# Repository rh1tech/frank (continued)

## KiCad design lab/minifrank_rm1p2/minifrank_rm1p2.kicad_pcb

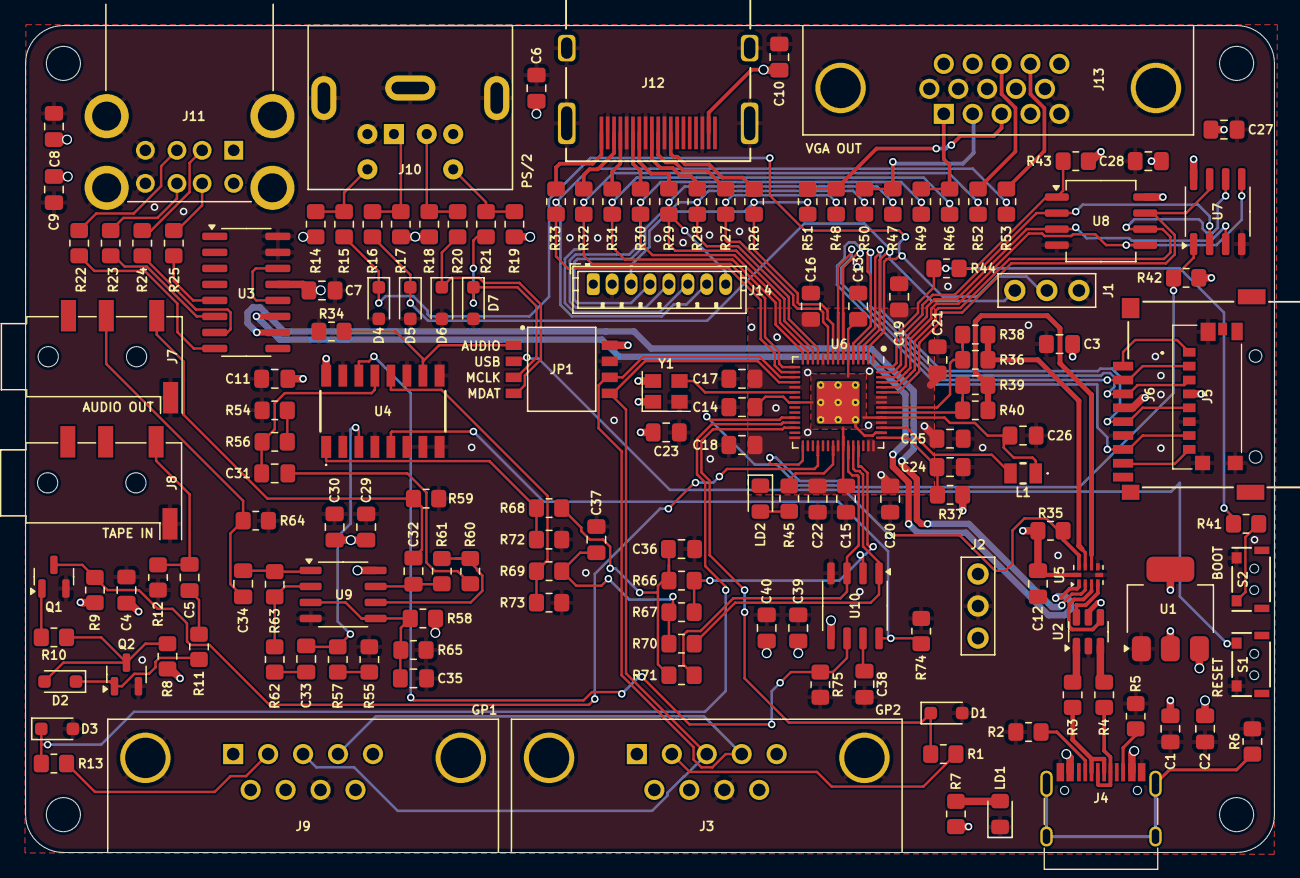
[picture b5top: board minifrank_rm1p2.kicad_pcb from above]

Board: 4 copper layers, 99.0 x 65.5 mm, 159 parts (0 on the bottom side), 116 nets.

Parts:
C1, C2, C8, C9, C29, C31, C32, C33, C34, C35, C38, C39: 10u; Capacitor (0805)
C3, C4, C5, C6, C10, C11, C12, C13, C15, C16, C17, C18, C19, C20, C21, C22, C23, C27, C28, C30, C40: 100n; Capacitor (0805)
C7, C14, C24, C25, C26: 4.7u; Capacitor (0805)
C36, C37: 47n; Capacitor (0805)
D1, D3, D4, D5, D6, D7: 3V3; Diode (SOD-323)
D2: 1N4148; Diode (SOD-323)
H1, H2, H3, H4: MountingHole; Mounting Hole (2.7mm)
J1: UART; Pin Header (1x03)
J2: PWR; Pin Header (1x03)
J3, J9: D-SUB 9 Male; D-SUB (9 pin, male, top mount)
J4: USB4215-03-A; USB Type C
J5: 0475710001; MicroSD (SMD, short)
J6: 104031-0811; MicroSD (SMD, long)
J7, J8: PJ-320D; Jack (3.5mm, PJ-320D)
J10: MDC-036; MiniDIN (6 Pin, female)
J11: SS-52100-004; USB Type A (stacked)
J12: DC3RX19JA2; HDMI (female)
J13: D-SUB 15 Female; D-SUB (15 pin, female)
J14: Pin Header 1x08; Connector Female ZH 1.50mm (8 pins)
JP1: Main Jumpers; SW_DS05-127-2-04BK-SMT-TR
L1: 3.3u; Inductor (0806)
LD1: Power; LED (0805)
LD2: Blue; LED (0805)
Q1, Q2: BC850; SOT-23
R1, R7, R9, R13, R14, R17, R18, R19, R41, R45, R49, R50, R51, R70, R71: 1K; Resistor (0805)
R2, R5: 5.1K; Resistor (0805)
R3, R4, R22, R23, R24, R25: 22R; Resistor (0805)
R6: 1M; Resistor (0805)
R8, R10, R11, R34, R35, R42, R43, R56, R57, R58, R60, R62, R65, R68, R69: 10K; Resistor (0805)
R12, R15, R16, R20, R21, R52, R53: 100R; Resistor (0805)
R26, R27, R28, R29, R30, R31, R32, R33: 270R; Resistor (0805)
R36, R39: 150R; Resistor (0805)
R37: 33; Resistor (0805)
R38, R40: 33R; Resistor (0805)
R44: 0R; Resistor (0805)
R46, R47, R48: 330R; Resistor (0805)
R54, R55, R66, R67, R72, R73: 2K; Resistor (0805)
R59, R64: 20K; Resistor (0805)
R61, R63: 47K; Resistor (0805)
R74, R75: 470R; Resistor (0805)
S1: Reset; TACT-SIDE-4623
S2: TS-1233; TACT-SIDE-4623
U1: NCP1117 3.3; SOT-223
U2: USBLC6-2SC6; SOT-23-6
U3: MW7211A; SOP-16
U4: 74HC4052D; 74HC4052D653
U5: TS3USB221RSER; UQFN-10
U6: RP2350; QFN 60 (RP2350A)
U7: ESP-PSRAM32; SO-8
U8: W25Q128JVS; SOIC-8
U9: LM358; SO-8
U10: TDA1387T; SO-8
Y1: ASE-12MHz; Crystal (3225, active)

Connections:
+1V1: C13.1, C14.1, C15.1, C26.1, L1.1, U6.6 (DVDD), U6.23 (DVDD), U6.39 (DVDD), U6.50 (VREG_FB)
+3V3: C1.1, C3.2, C4.1, C11.2, C12.2, C16.1, C17.1, C18.1, C19.1, C20.1, C21.1, C22.1, C23.1, C25.1, C27.1, C28.1, J2.1, J5.P4 (VDD), J6.4 (VDD), JP1.8, R7.2, R8.1, R9.1, R35.1, R37.1, R42.2, R43.1, U1.2 (VO), U4.16 (VCC), U5.10 (VCC), U6.1 (IOVDD), U6.11 (IOVDD), U6.20 (IOVDD), U6.30 (IOVDD), U6.38 (IOVDD), U6.44 (ADC_AVDD), U6.45 (IOVDD), U6.49 (VREG_VIN), U6.53 (USB_OTP_VDD), U6.54 (QSPI_IOVDD), U7.8 (VCC), U8.8 (VCC), Y1.1 (EN), Y1.4 (Vdd)
/AMP_IN_L: C31.1, R56.1, U4.13 (1Z)
/AMP_IN_R: C33.1, R57.1, U4.3 (2Z)
/AUDIOSW: JP1.1, R34.2, U4.10 (S0)
/Audio Out/AMP_OUTL: C32.2, J7.T, R59.2
/Audio Out/AMP_OUTR: C34.2, J7.R, R64.2
/D+: R36.1, R38.1, U5.8 (D+)
/D-: R39.1, R40.1, U5.7 (D-)
/GPIO0: D4.1 (K), J1.2, R15.2, U6.2 (GPIO0)
/GPIO1: D5.1 (K), J1.3, R16.2, U6.3 (GPIO1)
/GPIO2: J5.P5 (CLK), J6.5 (CLK), U6.4 (GPIO2)
/GPIO3: J5.P3 (CMD), J6.3 (CMD), U6.5 (GPIO3)
/GPIO4: J5.P7 (DAT0), J6.7 (DAT0), U6.7 (GPIO4)
/GPIO5: J5.P2 (CD/DAT3), J6.2 (DAT3/CD), U6.8 (GPIO5)
/GPIO6: J14.3, R26.2, R51.1, U6.9 (GPIO6)
/GPIO7: R27.2, R48.1, U6.10 (GPIO7)
/GPIO8: J14.4, R28.2, R50.1, U6.12 (GPIO8)
/GPIO9: J14.8, R29.2, R47.1, U6.13 (GPIO9)
/GPIO10: J14.5, R30.2, R49.1, U6.14 (GPIO10)
/GPIO11: R31.2, R46.1, U6.15 (GPIO11)
/GPIO12: J14.6, R32.2, R52.2, U6.16 (GPIO12)
/GPIO13: J14.7, R33.2, R53.2, U6.17 (GPIO13)
/GPIO14: J3.4, J9.4, JP1.6, U6.18 (GPIO14)
/GPIO15: J3.3, J9.3, JP1.5, U6.19 (GPIO15)
/GPIO16: D3.1 (K), R13.1, U6.27 (GPIO16)
/GPIO17: D1.1 (K), R1.1, U6.28 (GPIO17)
/GPIO19: R42.1, U6.31 (GPIO19), U7.1 (~CE)
/GPIO22: Q1.3 (C), R9.2, U6.34 (GPIO22)
/GPIO26: R71.2, U6.40 (GPIO26_ADC0), U10.3 (DATA)
/GPIO27: R70.2, U6.41 (GPIO27_ADC1), U10.1 (SCLK)
/GPIO28: R66.1, R67.1, U6.42 (GPIO28_ADC2), U10.2 (LRCK)
/HUB_D+: U3.11 (DPU), U5.1 (1D+)
/HUB_D-: U3.10 (DMU), U5.2 (1D-)
/KB_CLK: J10.5, R14.2, R15.1
/KB_DATA: J10.1, R16.1, R17.2
/MS_CLK: J10.6, R19.2, R21.1
/MS_CLK_3V: D7.1 (K), JP1.3, R21.2
/MS_DATA: J10.2, R18.2, R20.1
/MS_DATA_3V: D6.1 (K), JP1.4, R20.2
/PWM_OUT_L: R69.2, R73.1, U4.12 (1Y0)
/PWM_OUT_R: R68.2, R72.1, U4.1 (2Y0)
/RP2350A/FLASH_SS: R43.2, R44.2, U8.1 (~CS)
/RP2350A/QSPI_SCLK: U6.56 (QSPI_SCLK), U7.6 (SCLK), U8.6 (CLK)
/RP2350A/QSPI_SD0: U6.57 (QSPI_SD0), U7.5 (SI/SIO), U8.5 (DI(IO0))
/RP2350A/QSPI_SD1: U6.59 (QSPI_SD1), U7.2 (SO/SIO), U8.2 (DO(IO1))
/RP2350A/QSPI_SD2: U6.58 (QSPI_SD2), U7.3 (SIO2), U8.3 (IO2)
/RP2350A/QSPI_SD3: U6.55 (QSPI_SD3), U7.7 (SIO3), U8.7 (IO3)
/RP2350A/QSPI_SS: R41.1, R44.1, U6.60 (QSPI_SS)
/RP2350A/VREG_AVDD: C24.1, R37.2, U6.46 (VREG_AVDD)
/RP2350A/VREG_LX: L1.2, U6.48 (VREG_LX)
/RP2350A/XIN: U6.21 (XIN), Y1.3 (OUT)
/RP2350A/~USB_BOOT: R41.2, S2.2
/RUN: S1.1, U6.26 (RUN)
/SD Card/DAT1: J5.P8 (DAT1), J6.8 (DAT1)
/SD Card/DAT2: J5.P1 (DAT2), J6.1 (DAT2)
/TDA_L: R75.2, U4.14 (1Y1), U10.6 (A_LEFT)
/TDA_R: R74.1, U4.5 (2Y1), U10.8 (A_RIGHT)
/USBMPXSW: JP1.2, R35.2, U5.9 (S)
/USB_D1+: R22.1, U3.8 (DP3)
/USB_D1-: R24.1, U3.7 (DM3)
/USB_D2+: R23.1, U3.6 (DP2)
/USB_D2-: R25.1, U3.5 (DM2)
/UTC_D+: U2.4 (I/O2), U5.3 (2D+)
/UTC_D-: U2.6 (I/O1), U5.4 (2D-)
GND: C1.2, C2.2, C3.1, C4.2, C6.2, C7.2, C8.2, C9.2, C10.2, C11.1, C12.1, C13.2, C14.2, C15.2, C16.2, C17.2, C18.2, C19.2, C20.2, C21.2, C22.2, C23.2, C24.2, C25.2, C26.2, C27.2, C28.2, C29.1, C30.1, C35.1, C36.2, C37.2, C38.2, C39.2, C40.2, D1.2 (A), D3.2 (A), D4.2 (A), D5.2 (A), D6.2 (A), D7.2 (A), J1.1, J2.2, J3.8, J4.1 (GND), J4.12 (GND), J5.G1 (GND_1), J5.G2 (GND_2), J5.G3 (GND_3), J5.P6 (VSS), J6.6 (VSS), J7.S, J8.S, J9.8, J10.3, J11.4 (GND1), J11.8 (GND2), J11.9 (Shield), J12.2 (G_D2), J12.5 (G_D1), J12.8 (G_D0), J12.11 (G_CLK), J12.17 (G_DDC/CEC), J12.20 (SHIELD1), J12.21 (SHIELD2), J12.22 (SHIELD3), J12.23 (SHIELD4), J13.0, J13.5, J13.6, J13.7, J13.8, J13.10, J14.2, JP1.7, LD1.1 (K), LD2.1 (K), Q1.2 (E), Q2.2 (E), R2.1, R5.1, R6.2, R12.2, R34.1, R54.2, R55.2, R59.1, R64.1, R65.1, R72.2, R73.2, R74.2, R75.1, S1.2, S2.1, U1.1 (GND), U2.2 (GND), U3.15 (GND), U3.16 (GND), U4.2 (2Y2), U4.4 (2Y3), U4.6 (~E), U4.7 (VEE), U4.8 (GND), U4.9 (S1), U4.11 (1Y3), U4.15 (1Y2), U5.5 (GND), U5.6 (~OE), U6.47 (VREG_PGND), U6.61 (GND), U7.4 (VSS), U8.4 (GND), U9.4 (V-), U10.4 (AGND), Y1.2 (GND)
GPIO25: R45.2, U6.37 (GPIO25)
unnamed: C5.1, J8.T, R12.1
unnamed: C5.2, R11.1
unnamed: C31.2, R60.2
unnamed: C32.1, R61.1, U9.7
unnamed: C33.2, R62.2
unnamed: C34.1, R63.1, U9.1
unnamed: C36.1, R66.2, R68.1, R71.1
unnamed: C37.1, R67.2, R69.1, R70.1
unnamed: D2.2 (A), Q2.3 (C), R8.2, R10.1
unnamed: D2.1 (K), Q2.1 (B), R11.2
unnamed: J3.2, R1.2
unnamed: J4.4 (CC1), R2.2
unnamed: J4.10 (CC2), R5.2
unnamed: J4.5 (DN2), J4.7 (DN1), R3.2
unnamed: J4.6 (DP1), J4.8 (DP2), R4.2
unnamed: J4.13 (SHIELD), R6.1
unnamed: J9.2, R13.2
unnamed: J11.3 (D1+), R22.2
unnamed: J11.2 (D1-), R24.2
unnamed: J11.7 (D2+), R23.2
unnamed: J11.6 (D2-), R25.2
unnamed: J12.12 (CLKN), R26.1
unnamed: J12.10 (CLKP), R27.1
unnamed: J12.9 (D0N), R28.1
unnamed: J12.7 (D0P), R29.1
unnamed: J12.6 (D1N), R30.1
unnamed: J12.4 (D1P), R31.1
unnamed: J12.3 (D2N), R32.1
unnamed: J12.1 (D2P), R33.1
unnamed: J13.1, R46.2, R49.2
unnamed: J13.2, R47.2, R50.2
unnamed: J13.3, R48.2, R51.2
unnamed: J13.13, R52.1
unnamed: J13.14, R53.1
unnamed: LD1.2 (A), R7.1
unnamed: LD2.2 (A), R45.1
unnamed: Q1.1 (B), R10.2
unnamed: R3.1, U2.1 (I/O1)
unnamed: R4.1, U2.3 (I/O2)
unnamed: R54.1, R56.2
unnamed: R55.1, R57.2
unnamed: U3.12 (VD33), U3.14 (VD3)
unnamed: R39.2, R40.2, U6.51 (USB_DM)
unnamed: R36.2, R38.2, U6.52 (USB_DP)
unnamed: C35.2, R58.1, R65.2, U9.3 (+), U9.5 (+)
unnamed: R62.1, R63.2, U9.2 (-)
unnamed: R60.1, R61.2, U9.6 (-)
unnamed: C38.1, U10.7 (FLT)
VBUS: C2.1, C6.1, C7.1, C8.1, C9.1, C10.1, C29.2, C30.2, C39.1, C40.1, J2.3, J3.6, J4.2 (VBUS), J4.11 (VBUS), J9.6, J10.4, J11.1 (VBUS1), J11.5 (VBUS2), J12.18 (+5V), J14.1, R14.1, R17.1, R18.1, R19.1, R58.2, U1.3 (VI), U2.5 (VBUS), U3.13 (VDD5), U9.8 (V+), U10.5 (VA)

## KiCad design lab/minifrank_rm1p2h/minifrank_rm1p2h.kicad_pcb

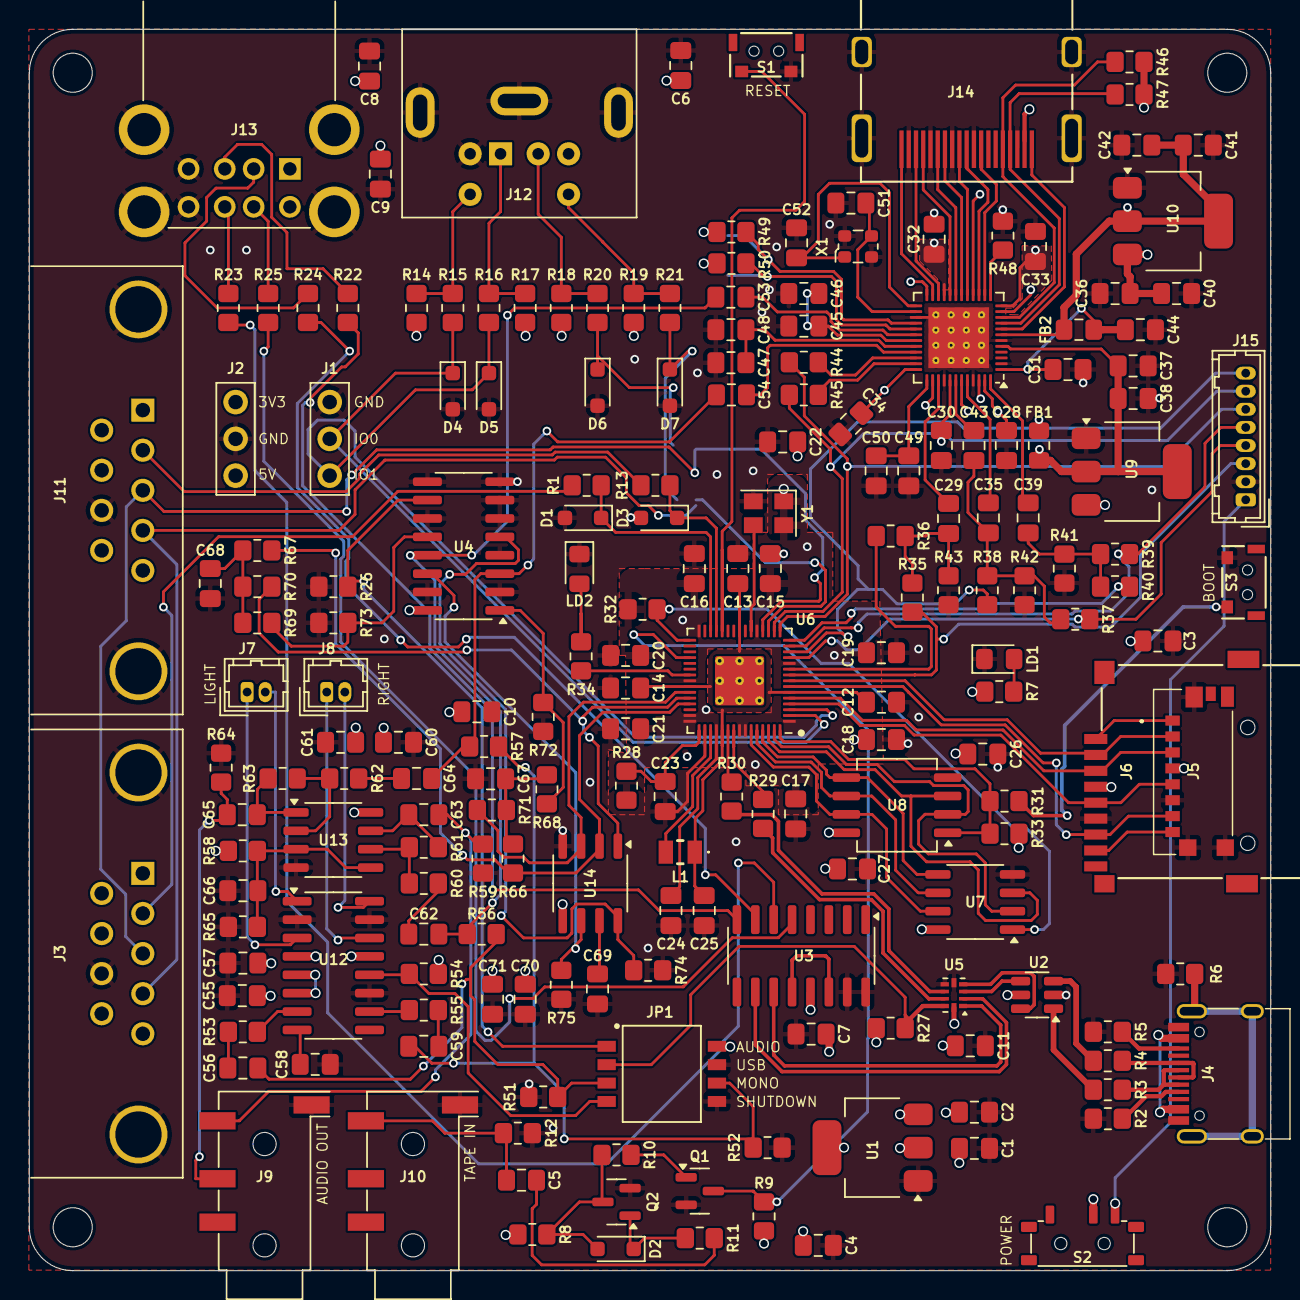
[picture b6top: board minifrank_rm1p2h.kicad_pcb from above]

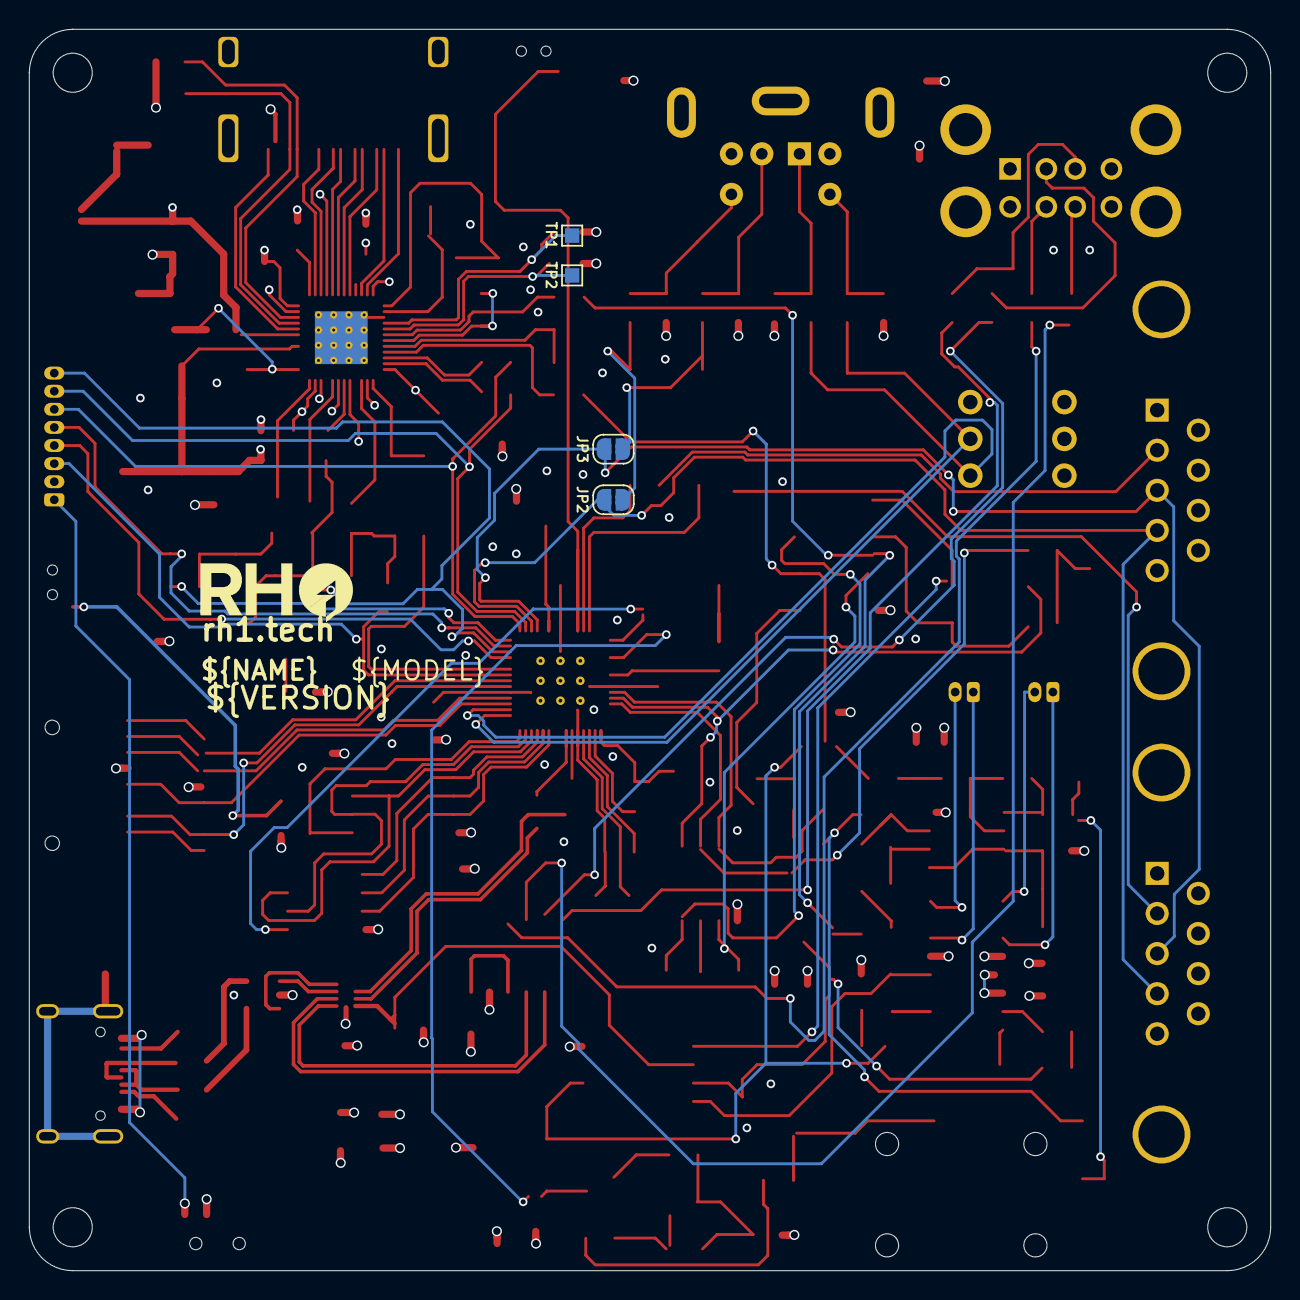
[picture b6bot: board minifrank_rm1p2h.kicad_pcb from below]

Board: 4 copper layers, 85.8 x 85.8 mm, 203 parts (4 on the bottom side), 148 nets.

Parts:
C1, C2, C8, C9, C28, C36, C37, C41, C44, C60, C62, C63, C64, C65, C66, C69, C70: 10u; Capacitor (0805)
C3, C4, C5, C6, C10, C11, C12, C14, C15, C16, C17, C18, C19, C20, C21, C22, C26, C27, C29, C30, C31, C32, C33, C34, C35, C39, C40, C58, C61, C71: 100n; Capacitor (0805)
C7, C13, C23, C24, C25, C46, C48, C50: 4.7u; Capacitor (0805)
C38, C42, C53, C54, C55, C56, C59: 1u; Capacitor (0805)
C43: 1n; Capacitor (0805)
C45, C47, C49: 220n; Capacitor (0805)
C51, C52: 15p; Capacitor (0805)
C57: 47u; Capacitor (0805)
C67, C68: 47n; Capacitor (0805)
D1, D3, D4, D5, D6, D7: 3V3; Diode (SOD-323)
D2: 1N4148; Diode (SOD-323)
FB1, FB2: 220R; Inductor (0805)
H1, H2, H3, H4: MountingHole; Mounting Hole (2.7mm)
J1: UART; Pin Header (1x03)
J2: PWR; Pin Header (1x03)
J3, J11: D-SUB 9 Male; D-SUB (9 pin, male, top mount)
J4: USB4215-03-A; USB Type C
J5: 0475710001; MicroSD (SMD, short)
J6: 104031-0811; MicroSD (SMD, long)
J7: PAM L; Connector Female 1.25 JST 2P
J8: PAM R; Connector Female 1.25 JST 2P
J9, J10: PJ-320D; Jack (3.5mm, PJ-320D)
J12: MDC-036; MiniDIN (6 Pin, female)
J13: SS-52100-004; USB Type A (stacked)
J14: DC3RX19JA2; HDMI (female)
J15: Pin Header 1x08; Connector Female 1.25 JST 8P
JP1: Main Jumpers; SW_DS05-127-2-04BK-SMT-TR
JP2: Mouse CLK; Jumper (solder)
JP3: Mouse DATA; Jumper (solder)
L1: 3.3u; Inductor (0806)
LD1: Power; LED (0805)
LD2: Blue; LED (0805)
Q1, Q2: BC850; SOT-23
R1, R7, R9, R13, R14, R17, R18, R19, R31, R34, R48, R70, R71: 1K; Resistor (0805)
R2, R5: 5.1K; Resistor (0805)
R3, R4, R22, R23, R24, R25: 22R; Resistor (0805)
R6: 1M; Resistor (0805)
R8, R10, R11, R26, R27, R32, R33, R53, R54, R55, R56, R57, R58, R60, R62, R65, R68, R69: 10K; Resistor (0805)
R12, R15, R16, R20, R21, R44, R45: 100R; Resistor (0805)
R28: 33; Resistor (0805)
R29, R30: 27R; Resistor (0805)
R35, R37, R39: 800R; Resistor (0805)
R36, R38, R40: 400R; Resistor (0805)
R41, R42, R43: 75R; Resistor (0805)
R46, R47, R51, R52, R66, R67, R72, R73: 2K; Resistor (0805)
R49, R50: 4.7K; Resistor (0805)
R59, R64: 20K; Resistor (0805)
R61, R63: 47K; Resistor (0805)
R74, R75: 470R; Resistor (0805)
S1: Reset; TACT-SIDE-4623
S2: MSK12C02; Switch (MSK12C02)
S3: TS-1233; TACT-SIDE-4623
TP1: MS9288_SCL; TestPoint (Pad 1.0x1.0mm)
TP2: MS9288_SDA; TestPoint (Pad 1.0x1.0mm)
U1: NCP1117 3.3; SOT-223
U2: USBLC6-2SC6; SOT-23-6
U3: MW7211A; SOP-16
U4: 74HC4052D; SOP-16
U5: TS3USB221RSER; UQFN-10
U6: RP2350; QFN 60 (RP2350A)
U7: ESP-PSRAM32; SO-8
U8: W25Q128JVS; SOIC-8
U9: AMS1117-3.3; SOT-223
U10: AMS1117-1.8; SOT-223
U11: MS9288A; QFN 48
U12: PAM8403D; SOP-16
U13: LM358; SO-8
U14: TDA1387T; SO-8
X1: 24.576 MHz; Crystal (2520)
Y1: ASE-12MHz; Crystal (3225, active)

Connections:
+1V1: C12.1, C13.1, C14.1, C25.1, L1.1, U6.6 (DVDD), U6.23 (DVDD), U6.39 (DVDD), U6.50 (VREG_FB)
+3V3: C1.1, C3.2, C4.1, C10.2, C11.2, C15.1, C16.1, C17.1, C18.1, C19.1, C20.1, C21.1, C22.1, C24.1, C26.1, C27.1, J2.1, J5.P4 (VDD), J6.4 (VDD), JP1.8, R7.2, R8.1, R9.1, R27.1, R28.1, R32.2, R33.1, U1.2 (VO), U4.16 (VCC), U5.10 (VCC), U6.1 (IOVDD), U6.11 (IOVDD), U6.20 (IOVDD), U6.30 (IOVDD), U6.38 (IOVDD), U6.44 (ADC_AVDD), U6.45 (IOVDD), U6.49 (VREG_VIN), U6.53 (USB_OTP_VDD), U6.54 (QSPI_IOVDD), U7.8 (VCC), U8.8 (VCC), Y1.1 (EN), Y1.4 (Vdd)
/AMP_IN_L: C53.2, C62.1, R56.1, U4.13 (1Z)
/AMP_IN_R: C54.2, C64.1, R57.1, U4.3 (2Z)
/AUDIOSW: JP1.1, R26.2, U4.10 (S0)
/Audio Out/AMP_OUTL: C63.2, J9.T, R59.2
/Audio Out/AMP_OUTR: C65.2, J9.R, R64.2
/Audio Out/AMP_PAM_OUTL_M: J7.2, U12.3 (-OUTL)
/Audio Out/AMP_PAM_OUTL_P: J7.1, U12.1 (+OUT_L)
/Audio Out/AMP_PAM_OUTR_M: J8.2, U12.14 (-OUT_R)
/Audio Out/AMP_PAM_OUTR_P: J8.1, U12.16 (+OUT_R)
/D+: R29.1, U5.8 (D+)
/D-: R30.1, U5.7 (D-)
/DAT1: J5.P8 (DAT1), J6.8 (DAT1)
/DAT2: J5.P1 (DAT2), J6.1 (DAT2)
/GPIO0: D4.1 (K), J1.2, R15.2, U6.2 (GPIO0)
/GPIO1: D5.1 (K), J1.3, R16.2, U6.3 (GPIO1)
/GPIO2: J5.P5 (CLK), J6.5 (CLK), U6.4 (GPIO2)
/GPIO3: J5.P3 (CMD), J6.3 (CMD), U6.5 (GPIO3)
/GPIO4: J5.P7 (DAT0), J6.7 (DAT0), U6.7 (GPIO4)
/GPIO5: J5.P2 (CD/DAT3), J6.2 (DAT3/CD), U6.8 (GPIO5)
/GPIO6: J15.3, R35.1, U6.9 (GPIO6)
/GPIO7: R36.1, U6.10 (GPIO7)
/GPIO8: J15.4, R37.1, U6.12 (GPIO8)
/GPIO9: J15.8, R38.1, U6.13 (GPIO9)
/GPIO10: J15.5, R39.1, U6.14 (GPIO10)
/GPIO11: R40.1, U6.15 (GPIO11)
/GPIO12: J15.6, R44.1, U6.16 (GPIO12)
/GPIO13: J15.7, R45.1, U6.17 (GPIO13)
/GPIO14: J3.4, J11.4, JP2.2 (B), U6.18 (GPIO14)
/GPIO15: J3.3, J11.3, JP3.2 (B), U6.19 (GPIO15)
/GPIO16: D3.1 (K), R13.1, U6.27 (GPIO16)
/GPIO17: D1.1 (K), R1.1, U6.28 (GPIO17)
/GPIO19: R32.1, U6.31 (GPIO19), U7.1 (~CE)
/GPIO22: Q1.3 (C), R9.2, U6.34 (GPIO22)
/GPIO26: R71.2, U6.40 (GPIO26_ADC0), U14.3 (DATA)
/GPIO27: R70.2, U6.41 (GPIO27_ADC1), U14.1 (SCLK)
/GPIO28: R66.1, R67.1, U6.42 (GPIO28_ADC2), U14.2 (LRCK)
/HUB_D+: U3.11 (DPU), U5.1 (1D+)
/HUB_D-: U3.10 (DMU), U5.2 (1D-)
/KB_CLK: J12.5, R14.2, R15.1
/KB_DATA: J12.1, R16.1, R17.2
/MONO_L: C56.1, JP1.3, R51.1, R56.2
/MONO_R: C59.1, JP1.6, R52.1, R57.2
/MS_CLK: J12.6, R19.2, R21.1
/MS_CLK_3V: D7.1 (K), JP2.1 (A), R21.2
/MS_DATA: J12.2, R18.2, R20.1
/MS_DATA_3V: D6.1 (K), JP3.1 (A), R20.2
/PWM_OUT_L: R69.2, R73.1, U4.12 (1Y0)
/PWM_OUT_R: R68.2, R72.1, U4.1 (2Y0)
/RP2350A/QSPI_SCLK: U6.56 (QSPI_SCLK), U7.6 (SCLK), U8.6 (CLK)
/RP2350A/QSPI_SD0: U6.57 (QSPI_SD0), U7.5 (SI/SIO), U8.5 (DI(IO0))
/RP2350A/QSPI_SD1: U6.59 (QSPI_SD1), U7.2 (SO/SIO), U8.2 (DO(IO1))
/RP2350A/QSPI_SD2: U6.58 (QSPI_SD2), U7.3 (SIO2), U8.3 (IO2)
/RP2350A/QSPI_SD3: U6.55 (QSPI_SD3), U7.7 (SIO3), U8.7 (IO3)
/RP2350A/QSPI_SS: R31.1, R33.2, U6.60 (QSPI_SS), U8.1 (~CS)
/RP2350A/VREG_AVDD: C23.1, R28.2, U6.46 (VREG_AVDD)
/RP2350A/VREG_LX: L1.2, U6.48 (VREG_LX)
/RP2350A/XIN: U6.21 (XIN), Y1.3 (OUT)
/RP2350A/~USB_BOOT: R31.2, S3.2
/RUN: S1.1, U6.26 (RUN)
/SHND: JP1.4, R54.2, U12.12 (SHND)
/TDA_L: R75.2, U4.14 (1Y1), U14.6 (A_LEFT)
/TDA_R: R74.1, U4.5 (2Y1), U14.8 (A_RIGHT)
/USBMPXSW: JP1.2, R27.2, U5.9 (S)
/USB_D1+: R22.1, U3.8 (DP3)
/USB_D1-: R24.1, U3.7 (DM3)
/USB_D2+: R23.1, U3.6 (DP2)
/USB_D2-: R25.1, U3.5 (DM2)
/UTC_D+: U2.4 (I/O2), U5.3 (2D+)
/UTC_D-: U2.6 (I/O1), U5.4 (2D-)
/VGA/ALIN: C53.1, U11.30 (ALIN)
/VGA/AMS_1V8: C32.1, C41.1, C42.1, FB2.1, U10.2 (VO), U11.7 (AVDD18), U11.16 (AVDD18), U11.21 (AVDD18)
/VGA/AMS_1V8A: C30.1, C31.1, C44.1, FB2.2, U11.1 (AVDD18_ADC), U11.41 (AVDD18_ADC), U11.46 (AVDD18_ADC)
/VGA/AMS_3V3: C34.1, C37.1, C38.1, FB1.2, U9.2 (VO), U11.5 (DVDD33), U11.11 (DVDD33), U11.24 (DVDD33), U11.36 (DVDD33)
/VGA/AMS_3V3A: C28.1, C33.1, FB1.1, U11.12 (AVDD33), U11.38 (AVDD33), U11.43 (AVDD33), U11.47 (AVDD33)
/VGA/ARIN: C54.1, U11.33 (ARIN)
/VGA/B: C29.1, U11.39 (B/Pb)
/VGA/DCCSCL: J14.15 (SCL), R46.1, U11.10 (DCCSCL)
/VGA/DDCSDA: J14.16 (SDA), R47.1, U11.9 (DDCSDA)
/VGA/G: C35.1, U11.44 (G/Y)
/VGA/HDMI_5V: J14.18 (+5V), R46.2, R47.2
/VGA/HPDT: J14.19 (HOT_PLUG_DET), U11.8 (HotPlugDetect)
/VGA/R: C39.1, U11.48 (R/Pr)
/VGA/SCL: R49.1, TP1.1, U11.28 (SCL)
/VGA/SDA: R50.1, TP2.1, U11.29 (SDA)
/VGA/SOG_G: C35.2, C43.2, R37.2, R38.2, R42.1
/VGA/TMDS_CLK+: J14.10 (CLKP), U11.15 (TMDS_CLK+)
/VGA/TMDS_CLK-: J14.12 (CLKN), U11.14 (TMDS_CLK-)
/VGA/TMDS_D0+: J14.7 (D0P), U11.18 (TMDS-D0+)
/VGA/TMDS_D0-: J14.9 (D0N), U11.17 (TMDS_D0-)
/VGA/TMDS_D1+: J14.4 (D1P), U11.20 (TMDS_D1+)
/VGA/TMDS_D1-: J14.6 (D1N), U11.19 (TMDS_D1-)
/VGA/TMDS_D2+: J14.1 (D2P), U11.23 (TMDS_D2+)
/VGA/TMDS_D2-: J14.3 (D2N), U11.22 (TMDS_D2-)
GND: C1.2, C2.2, C3.1, C4.2, C6.2, C7.2, C8.2, C9.2, C10.1, C11.1, C12.2, C13.2, C14.2, C15.2, C16.2, C17.2, C18.2, C19.2, C20.2, C21.2, C22.2, C23.2, C24.2, C25.2, C26.2, C27.2, C28.2, C30.2, C31.2, C32.2, C33.2, C34.2, C36.2, C37.2, C38.2, C40.2, C41.2, C42.2, C44.2, C45.2, C46.2, C47.2, C48.2, C49.2, C50.2, C51.2, C52.2, C55.2, C57.2, C58.2, C60.1, C61.1, C66.1, C67.2, C68.2, C69.2, C70.2, C71.2, D1.2 (A), D3.2 (A), D4.2 (A), D5.2 (A), D6.2 (A), D7.2 (A), J1.1, J2.2, J3.8, J4.1 (GND), J4.12 (GND), J5.G1 (GND_1), J5.G2 (GND_2), J5.G3 (GND_3), J5.P6 (VSS), J6.6 (VSS), J9.S, J10.S, J11.8, J12.3, J13.4 (GND1), J13.8 (GND2), J13.9 (Shield), J14.2 (G_D2), J14.5 (G_D1), J14.8 (G_D0), J14.11 (G_CLK), J14.17 (G_DDC/CEC), J14.20 (SHIELD1), J14.21 (SHIELD2), J14.22 (SHIELD3), J14.23 (SHIELD4), J15.1, JP1.5, JP1.7, LD1.1 (K), LD2.1 (K), Q1.2 (E), Q2.2 (E), R2.1, R5.1, R6.2, R12.2, R26.1, R41.2, R42.2, R43.2, R48.1, R51.2, R52.2, R59.1, R64.1, R65.1, R72.2, R73.2, R74.2, R75.1, S1.2, S3.1, U1.1 (GND), U2.2 (GND), U3.15 (GND), U3.16 (GND), U4.2 (2Y2), U4.4 (2Y3), U4.6 (~E), U4.7 (VEE), U4.8 (GND), U4.9 (S1), U4.11 (1Y3), U4.15 (1Y2), U5.5 (GND), U5.6 (~OE), U6.47 (VREG_PGND), U6.61 (GND), U7.4 (VSS), U8.4 (GND), U9.1 (GND), U10.1 (GND), U11.2 (GND), U11.6 (GND), U11.27 (GND), U11.40 (GND), U11.45 (GND), U11.49 (EP), U12.2 (PGND), U12.11 (GND), U12.15 (PGND), U13.4 (V-), U14.4 (AGND), X1.2 (GND), X1.4 (GND), Y1.2 (GND)
GPIO25: R34.2, U6.37 (GPIO25)
unnamed: C5.1, J10.T, R12.1
unnamed: C5.2, R11.1
unnamed: C29.2, R35.2, R36.2, R43.1
unnamed: C39.2, R39.2, R40.2, R41.1
unnamed: C56.2, R53.2
unnamed: C59.2, R55.2
unnamed: C62.2, R60.2
unnamed: C63.1, R61.1, U13.7
unnamed: C64.2, R62.2
unnamed: C65.1, R63.1, U13.1
unnamed: C67.1, R66.2, R68.1, R71.1
unnamed: C68.1, R67.2, R69.1, R70.1
unnamed: D2.2 (A), Q2.3 (C), R8.2, R10.1
unnamed: D2.1 (K), Q2.1 (B), R11.2
unnamed: J3.2, R1.2
unnamed: J4.4 (CC1), R2.2
unnamed: J4.10 (CC2), R5.2
unnamed: J4.5 (DN2), J4.7 (DN1), R3.2
unnamed: J4.6 (DP1), J4.8 (DP2), R4.2
unnamed: J4.13 (SHIELD), R6.1
unnamed: J11.2, R13.2
unnamed: J13.3 (D1+), R22.2
unnamed: J13.2 (D1-), R24.2
unnamed: J13.7 (D2+), R23.2
unnamed: J13.6 (D2-), R25.2
unnamed: LD1.2 (A), R7.1
unnamed: LD2.2 (A), R34.1
unnamed: Q1.1 (B), R10.2
unnamed: R3.1, U2.1 (I/O1)
unnamed: R4.1, U2.3 (I/O2)
unnamed: J4.2 (VBUS), J4.11 (VBUS), S2.2 (B)
unnamed: U3.12 (VD33), U3.14 (VD3)
unnamed: R30.2, U6.51 (USB_DM)
unnamed: R29.2, U6.52 (USB_DP)
unnamed: R44.2, U11.34 (HSIN)
unnamed: C49.1, C50.1, U11.37 (REFP)
unnamed: C45.1, C46.1, U11.31 (REFQ0)
unnamed: C47.1, C48.1, U11.32 (REFQ1)
unnamed: C43.1, U11.42 (SOG/Y)
unnamed: R48.2, U11.13 (SWREF1k)
unnamed: R45.2, U11.35 (VSIN)
unnamed: C52.1, U11.25 (XTI), X1.1 (OSC)
unnamed: C51.1, U11.26 (XTO), X1.3 (OSC)
unnamed: R53.1, U12.7 (INL)
unnamed: R55.1, U12.10 (INR)
unnamed: C58.1, U12.8 (VREF)
unnamed: C66.2, R58.1, R65.2, U13.3 (+), U13.5 (+)
unnamed: R62.1, R63.2, U13.2 (-)
unnamed: R60.1, R61.2, U13.6 (-)
unnamed: C69.1, U14.7 (FLT)
VBUS: C2.1, C6.1, C7.1, C8.1, C9.1, C36.1, C40.1, C55.1, C57.1, C60.2, C61.2, C70.1, C71.1, J2.3, J3.6, J11.6, J12.4, J13.1 (VBUS1), J13.5 (VBUS2), J15.2, R14.1, R17.1, R18.1, R19.1, R49.2, R50.2, R54.1, R58.2, S2.3 (A), U1.3 (VI), U2.5 (VBUS), U3.13 (VDD5), U9.3 (VI), U10.3 (VI), U12.4 (PVDD), U12.5 (MUTE), U12.6 (VDD), U12.13 (PVDD), U13.8 (V+), U14.5 (VA)
